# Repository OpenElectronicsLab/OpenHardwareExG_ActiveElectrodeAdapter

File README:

# OpenHardwareExG_ActiveElectrodeAdapter

This is an adapter board to simplify connecting one or more
OpenHardwareExG_ActiveElectrode s to devices that used 0.1 inch pitch
connectors such as the OpenHardwareExG_Shield or a breadboard.

This project is in early development and is not yet ready for use.

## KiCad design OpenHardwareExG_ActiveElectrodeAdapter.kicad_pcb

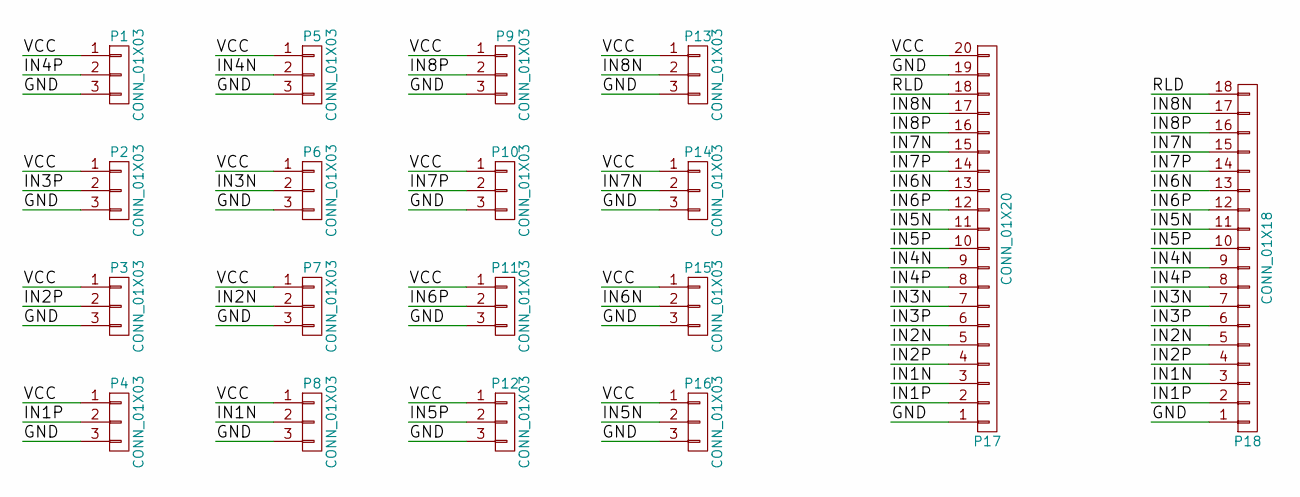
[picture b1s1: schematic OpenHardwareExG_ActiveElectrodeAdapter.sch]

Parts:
P1, P2, P3, P4, P5, P6, P7, P8, P9, P10, P11, P12, P13, P14, P15, P16: CONN_01X03; DF50A-3P-1V
P17: CONN_01X20; Pin_Header_Straight_1x20
P18: CONN_01X18; Pin_Header_Straight_1x18

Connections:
/GND: P1.3, P2.3, P3.3, P4.3, P5.3, P6.3, P7.3, P8.3, P9.3, P10.3, P11.3, P12.3, P13.3, P14.3, P15.3, P16.3, P17.1, P17.19, P18.1
/IN1N: P8.2, P17.3, P18.3
/IN1P: P4.2, P17.2, P18.2
/IN2N: P7.2, P17.5, P18.5
/IN2P: P3.2, P17.4, P18.4
/IN3N: P6.2, P17.7, P18.7
/IN3P: P2.2, P17.6, P18.6
/IN4N: P5.2, P17.9, P18.9
/IN4P: P1.2, P17.8, P18.8
/IN5N: P16.2, P17.11, P18.11
/IN5P: P12.2, P17.10, P18.10
/IN6N: P15.2, P17.13, P18.13
/IN6P: P11.2, P17.12, P18.12
/IN7N: P14.2, P17.15, P18.15
/IN7P: P10.2, P17.14, P18.14
/IN8N: P13.2, P17.17, P18.17
/IN8P: P9.2, P17.16, P18.16
/RLD: P17.18, P18.18; also elsewhere on the board
/VCC: P1.1, P2.1, P3.1, P4.1, P5.1, P6.1, P7.1, P8.1, P9.1, P10.1, P11.1, P12.1, P13.1, P14.1, P15.1, P16.1, P17.20

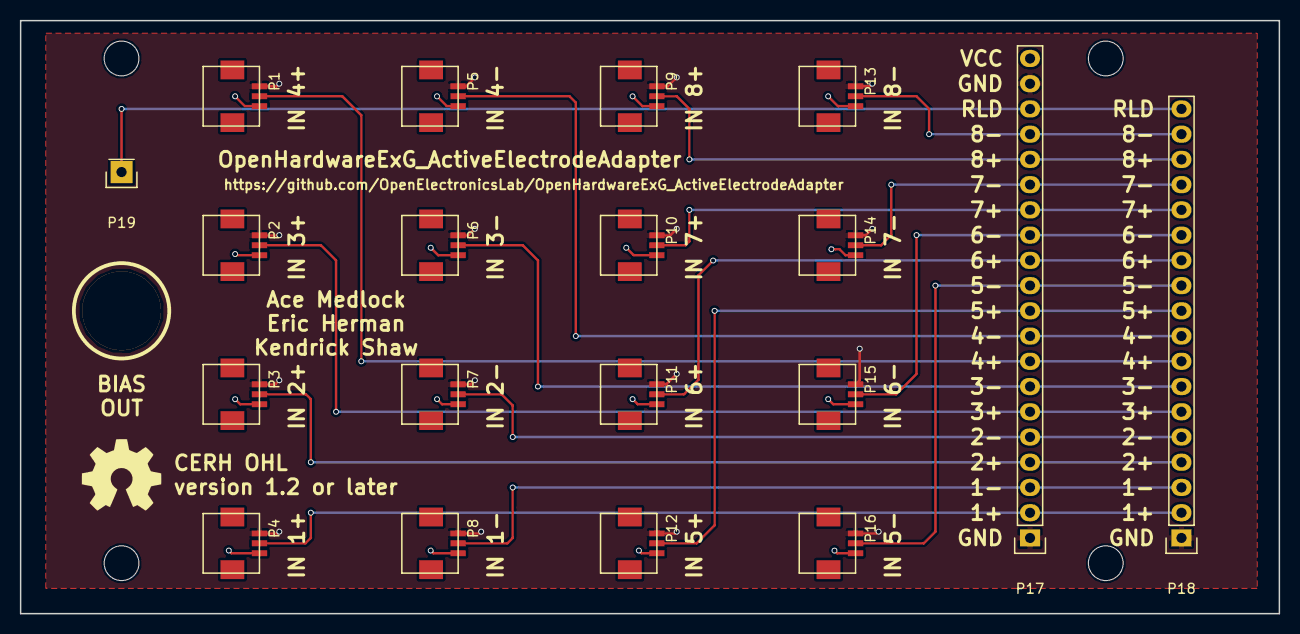
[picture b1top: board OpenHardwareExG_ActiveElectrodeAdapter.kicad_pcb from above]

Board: 4 copper layers, 126.7 x 59.7 mm, 24 parts (0 on the bottom side), 19 nets.

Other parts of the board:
HOLE1, HOLE2, HOLE3, HOLE4: MountingHole_3-5mm
P19: CONN_01X01; Pin_Header_Straight_1x01
Touchproof-socket: VAL**; Touchproof-socket-spacer

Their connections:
/RLD: P19.1; also elsewhere on the board

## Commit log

2016-02-06 initial commit with schematic
2016-02-14 set pin1 to be GND on breakout connectors, and align pin numbers
2016-02-14 add component DF50A-3P-1V footprint
    http://www.mouser.com/ds/2/185/HIrose_DF50%20Series-341565.pdf
2016-02-14 most PCB routing done.
2016-02-20 add RLD
2016-02-20 add labels for electrodes
2016-02-20 add labels to pins and headers
2016-02-20 add CERN OHL v1.2 (or later) license and logo
2016-02-20 add gerbers
2016-02-20 add BOM
